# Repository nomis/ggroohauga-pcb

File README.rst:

Logitech® Z906 Surround Sound Speakers
======================================

Overview
--------

PCBs for an alternative console and simulated amplifier interface for the
ESP32-S3 microcontroller interacting with Logitech® Z906 Surround Sound
Speakers.

    Glod picked up his horn. Cliff sat down and found his hammers. Buddy walked
    to the centre of the stage and, to Cliff's amazement, just stood there
    looking down at his feet.

    The cheering began to subside. And then it died away altogether. The huge
    hall was filled with the hush of hundreds of people holding their breath.

    Buddy's fingers moved. He picked out three simple little chords. And then he
    looked up.

    "Hello, Ankh-Morpork!"

    Cliff felt the music rise up behind him and rush him forward into a tunnel
    of fire and sparks and excitement. He brought his hammers down. And it was
    Music With Rocks In.

    -- `Terry Pratchett <https://en.wikipedia.org/wiki/Terry_Pratchett>`_
    (`Soul Music, 1994 <https://en.wikipedia.org/wiki/Soul_Music_(novel)>`_)

Purpose
-------

Provide an unofficial alternative console (to control the amplifier directly
without the original console) and simulated amplifier interface (to indirectly
control an amplifier with the original console).

Usage
-----

This project is made up of 3 KiCad projects, each of which share the same common
schematic file. These projects depend on support for symbolic links (which
can be enabled in Developer Mode if you're using Windows).

Schematic
---------

Common schematic shared by all PCBs. Components with an "A-" (amplifier)
reference are for the amplifier/bridge PCBs, components with a "C-" (console)
reference are for the console/bridge PCBs and components with an "S-" (single
DE-15 socket) reference are for the amplifier/console PCBs.

.. image:: render/ggroohauga-shared-sch.svg
   :alt: Common schematic

Amplifier PCB
~~~~~~~~~~~~~

Connect to an amplifier on its own to control the amplifier and access the Aux
Input and Headphones audio through `3.5mm TRS sockets <https://en.wikipedia.org/wiki/Phone_connector_(audio)>`_.

Dimensions: 95mm W × 31mm H

.. image:: render/ggroohauga-amplifier-pcb.svg
   :alt: Front and back of amplifier PCB

.. image:: render/ggroohauga-amplifier-sch.svg
   :alt: Amplifier-specific schematic

Console PCB
~~~~~~~~~~~

Connect to a console on its own to control the console and access the Aux Input
and Headphones audio through `3.5mm TRS sockets <https://en.wikipedia.org/wiki/Phone_connector_(audio)>`_.

Dimensions: 95mm W × 31mm H

.. image:: render/ggroohauga-console-pcb.svg
   :alt: Front and back of console PCB

.. image:: render/ggroohauga-console-sch.svg
   :alt: Console-specific schematic

Bridge PCB
~~~~~~~~~~

Connect between an amplifier and a console to control both devices
independently.

Dimensions: 98.5mm W × 31mm H

.. image:: render/ggroohauga-bridge-pcb.svg
   :alt: Front and back of bridge PCB

.. image:: render/ggroohauga-bridge-sch.svg
   :alt: Bridge-specific schematic

Components
----------

+-------+--------------------------------------------------------+--------------------+
| Ref   | Name                                                   | PCB                |
+=======+========================================================+====================+
|       | ESP32-S3 Development Board                             | all                |
+-------+--------------------------------------------------------+--------------------+
| S3L1  | 1x20 Pin Socket, Through Hole (2.54mm)                 | all                |
+-------+--------------------------------------------------------+--------------------+
| S3R1  | 1x20 Pin Socket, Through Hole (2.54mm)                 | all                |
+-------+--------------------------------------------------------+--------------------+
| A-C1  | 0.1µF Capacitor, SMD 0805 (Metric 2012)                | amplifier, bridge  |
+-------+--------------------------------------------------------+--------------------+
| A-C2  | 0.1µF Capacitor, SMD 0805 (Metric 2012)                | amplifier, bridge  |
+-------+--------------------------------------------------------+--------------------+
| A-J1  | Amphenol L77HDE15SD1CH4R DE-15 socket                  | amplifier, bridge  |
+-------+--------------------------------------------------------+--------------------+
| A-R1  | 1kΩ Resistor, SMD 0805 (Metric 2012)                   | amplifier, bridge  |
+-------+--------------------------------------------------------+--------------------+
| A-R2  | 10kΩ Resistor, SMD 0805 (Metric 2012)                  | amplifier, bridge  |
+-------+--------------------------------------------------------+--------------------+
| A-R3  | 10kΩ Resistor, SMD 0805 (Metric 2012)                  | amplifier, bridge  |
+-------+--------------------------------------------------------+--------------------+
| A-U1  | Texas Instruments ISO6742DWR Digital Isolator, SOIC-16 | amplifier, bridge  |
+-------+--------------------------------------------------------+--------------------+
| C-J1  | Amphenol L717HDE15PD1CH4F DE-15 plug                   | console, bridge    |
+-------+--------------------------------------------------------+--------------------+
| C-Q1  | Diodes DMP2004K P-Channel MOSFET, SOT-23-3             | console, bridge    |
+-------+--------------------------------------------------------+--------------------+
| S-J1  | Same Sky SJ1-3523N 3.5mm Audio Jack                    | amplifier, console |
+-------+--------------------------------------------------------+--------------------+
| S-J2  | Same Sky SJ1-3523N 3.5mm Audio Jack                    | amplifier, console |
+-------+--------------------------------------------------------+--------------------+

Supported ESP32-S3 Boards
-------------------------

* WEMOS LOLIN S3
* Espressif ESP32-S3-DevKitC-1
* Espressif ESP32-S3-DevKitM-1

Amplifier Signals GPIOs
~~~~~~~~~~~~~~~~~~~~~~~

"Amplifier Power In" should only be pulled down, to avoid back-powering the
amplifier microcontroller when mains power is off.

When "Amplifier Power In" is active, the amplifier has mains power. Enable
"Console Announce" to turn the amplifier on, and disable it turn the amplifier
off. Don't leave it on constantly because it will heat up and waste power.
Automatic standby can be implemented by
`reading the idle time <https://github.com/nomis/logitech-z906/blob/main/protocol.rst#read-idle-time>`_.

When "Amplifier Detect" is active, the amplifier is ready to communicate over
the 3.3V UART. The labels "Amplifier RX" and "Amplifier TX" are from the
perspective of the amplifier.

+------------------------+-------+---------+-----------+-----------+----------+----------+
| Name                   |  Pin  |  LOLIN  |  DevKitC  |  DevKitM  |  Socket  |  Active  |
+========================+=======+=========+===========+===========+==========+==========+
| Amplifier Power In     |   11  |    8    |     8     |    10     |   L 12   |   High   |
+------------------------+-------+---------+-----------+-----------+----------+----------+
| Console Announce       |   15  |   41    |    41     |    42     |   R  7   |   Low    |
+------------------------+-------+---------+-----------+-----------+----------+----------+
| Amplifier Detect       |    8  |   21    |    21     |    21     |   R 15   |   Low    |
+------------------------+-------+---------+-----------+-----------+----------+----------+
| Amplifier RX           |   13  |   10    |    10     |    14     |   L 16   |          |
+------------------------+-------+---------+-----------+-----------+----------+----------+
| Amplifier TX           |   12  |    9    |     9     |    13     |   L 15   |          |
+------------------------+-------+---------+-----------+-----------+----------+----------+
| 3.3V                   |       |         |           |           |   L  1   |          |
+------------------------+-------+---------+-----------+-----------+----------+----------+
| GND                    |    6  |         |           |           |   R  1   |          |
+------------------------+-------+---------+-----------+-----------+----------+----------+

Console Signals GPIOs
~~~~~~~~~~~~~~~~~~~~~

Prepare all other GPIOs and UARTs before applying console power, otherwise it
will report a communication error.

Enable "Console Power out" to power the console on, and disable it to power off
the console. Without a `firmware modification to the console <https://github.com/nomis/logitech-z906/blob/main/firmware.rst#automatic-power-on>`_,
user intervention will be required to turn the console on after it's powered.

When "Amplifier Announce" is active, the amplifier indicates that it is ready to
communicate over the 3.3V UART. The labels "Console RX" and "Console TX" are
from the perspective of the console.

+------------------------+-------+---------+-----------+-----------+----------+----------+
| Name                   |  Pin  |  LOLIN  |  DevKitC  |  DevKitM  |  Socket  |  Active  |
+========================+=======+=========+===========+===========+==========+==========+
| Console Power Out      |   11  |   40    |    40     |    41     |   R  8   |   Low    |
+------------------------+-------+---------+-----------+-----------+----------+----------+
| Console RX             |   12  |    4    |     4     |     2     |   L  4   |          |
+------------------------+-------+---------+-----------+-----------+----------+----------+
| Console TX             |   13  |    6    |     6     |     4     |   L  6   |          |
+------------------------+-------+---------+-----------+-----------+----------+----------+
| Amplifier Announce     |    8  |   13    |    47     |    26     |   R 17   |   Low    |
+------------------------+-------+---------+-----------+-----------+----------+----------+
| Console Detect         |   15  |   17    |    17     |     8     |   L 10   |   Low    |
+------------------------+-------+---------+-----------+-----------+----------+----------+
| 3.3V                   |       |         |           |           |   L  1   |          |
+------------------------+-------+---------+-----------+-----------+----------+----------+
| GND                    |    6  |         |           |           |   R  1   |          |
+------------------------+-------+---------+-----------+-----------+----------+----------+

Board ID GPIOs
~~~~~~~~~~~~~~

To identify which type of PCB the ESP32-S3 has been connected to, read the
big-endian value of these GPIOs.

+-------+---------+-----------+-----------+
|  Bit  |  LOLIN  |  DevKitC  |  DevKitM  |
+=======+=========+===========+===========+
|   2   |    7    |     7     |     5     |
+-------+---------+-----------+-----------+
|   1   |   15    |    15     |     6     |
+-------+---------+-----------+-----------+
|   0   |   16    |    16     |     7     |
+-------+---------+-----------+-----------+

+---------+-----------+
| Value   | PCB       |
+=========+===========+
| 000 (0) | Amplifier |
+---------+-----------+
| 001 (1) | Bridge    |
+---------+-----------+
| 010 (2) | Console   |
+---------+-----------+

Related Documentation
---------------------

* `Console firmware/interface/protocol <https://github.com/nomis/logitech-z906>`_

Related Software
----------------

* `Software to interact with the console/amplifier <https://github.com/nomis/ggroohauga>`_

Notices
-------

"Logitech" is a trademark of `Logitech International SA <https://www.logitech.com/>`_.

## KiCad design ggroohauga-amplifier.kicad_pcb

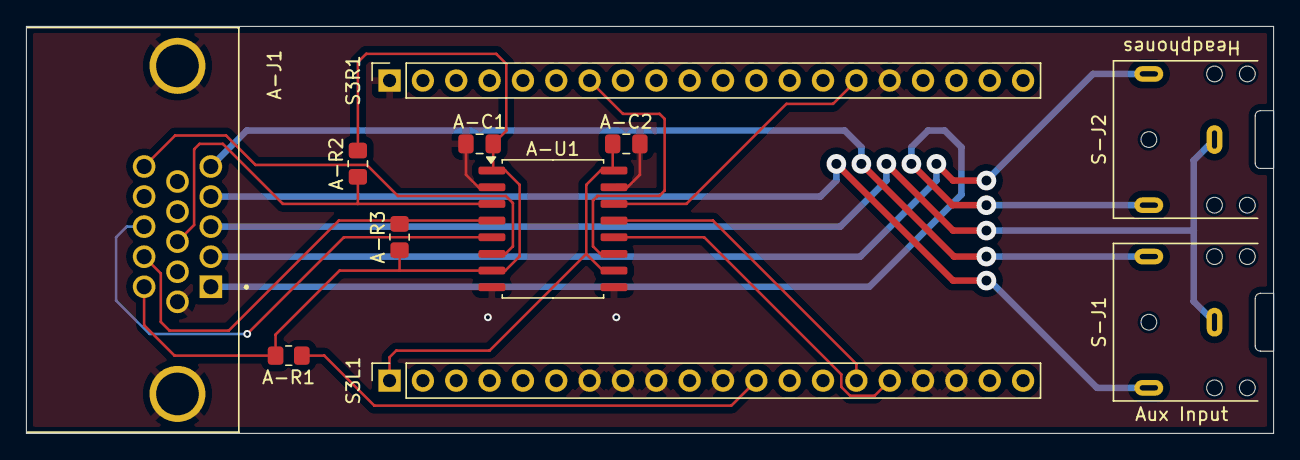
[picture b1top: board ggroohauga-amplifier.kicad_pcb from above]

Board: 2 copper layers, 95.0 x 31.0 mm, 12 parts (1 on the bottom side), 17 nets.

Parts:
A-C1, A-C2: 0.1µF; C_0805_2012Metric_Pad1.18x1.45mm_HandSolder
A-J1: DE15_Socket_HighDensity_MountingHoles; AMPHENOL_L77HDE15SD1CH4R
A-R1: 1kΩ; R_0805_2012Metric_Pad1.20x1.40mm_HandSolder
A-R2, A-R3: 10kΩ; R_0805_2012Metric_Pad1.20x1.40mm_HandSolder
A-U1: ISO6742; SOIC-16W_7.5x10.3mm_P1.27mm
MUSICWITHROCKSIN: LOGO
S3L1, S3R1: Conn_01x20_Socket; PinSocket_1x20_P2.54mm_Vertical
S-J1: Aux Input; Jack_3.5mm_CUI_SJ1-3523N_Horizontal
S-J2: Headphones; Jack_3.5mm_CUI_SJ1-3523N_Horizontal

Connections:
+3.3V: A-C2.1, A-U1.10 (EN2), A-U1.16 (V_{CC2}), S3L1.1
/Common/AMP_POWER_IN: A-C1.1, A-J1.11, A-R1.2, A-R2.2, A-R3.1, A-U1.1 (V_{CC1}), A-U1.7 (EN1)
/Common/AMP_RX: A-J1.13, A-U1.5 (OUTC)
/Common/AMP_TX: A-J1.12, A-R3.2, A-U1.4 (INB)
/Common/GPIO_L8_C8_M10/AMP_POWER_IN: A-R1.1, S3L1.12
/Common/GPIO_L9_C9_M13/AMP_TX: A-U1.13 (OUTB), S3L1.15
/Common/GPIO_L10_C10_M14/AMP_RX: A-U1.12 (INC), S3L1.16
/Common/~AMP_DETECT: A-J1.8, A-R2.1, A-U1.3 (INA)
/Common/~CON_ANNOUNCE: A-J1.15, A-U1.6 (OUTD)
/Common/~GPIO_L21_C21_M21/AMP_DETECT: A-U1.14 (OUTA), S3R1.15
/Common/~GPIO_L41_C41_M42/CON_ANNOUNCE: A-U1.11 (IND), S3R1.7
AUDIO_AUX_L: A-J1.5, S-J1.T
AUDIO_AUX_R: A-J1.4, S-J1.R
AUDIO_GROUND: A-J1.3, S-J1.S, S-J2.S
AUDIO_HEADPHONES_L: A-J1.2, S-J2.T
AUDIO_HEADPHONES_R: A-J1.1, S-J2.R
GND: A-C1.2, A-C2.2, A-J1.0, A-J1.6, A-U1.2 (GND1), A-U1.8 (GND1), A-U1.9 (GND2), A-U1.15 (GND2), S3L1.7, S3L1.8, S3L1.9, S3L1.11, S3L1.17, S3L1.18, S3R1.1, S3R1.16

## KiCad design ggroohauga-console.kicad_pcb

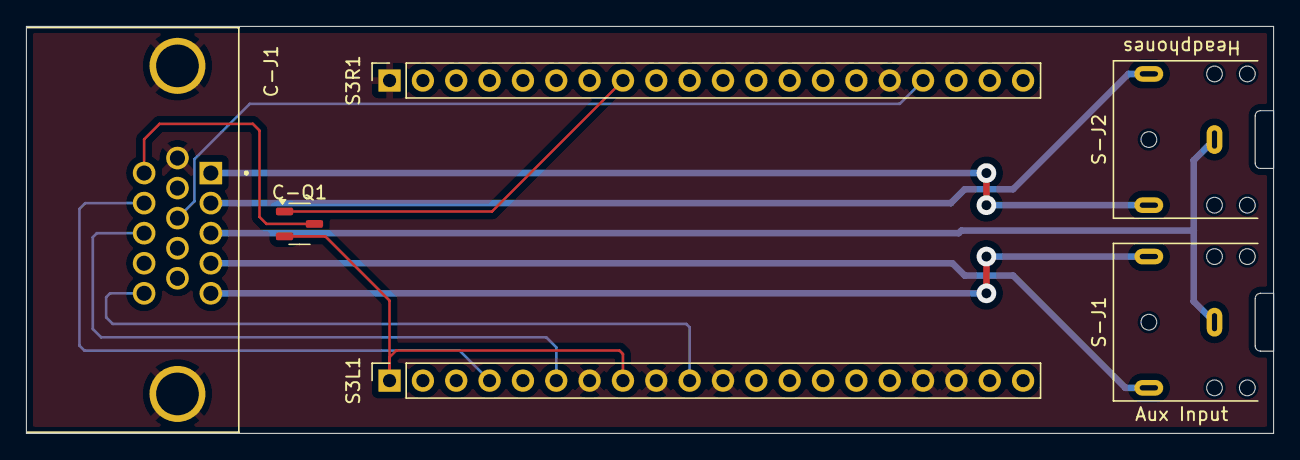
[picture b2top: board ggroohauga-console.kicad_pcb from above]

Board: 2 copper layers, 95.0 x 31.0 mm, 7 parts (1 on the bottom side), 13 nets.

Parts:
C-J1: DE15_Pins_HighDensity_MountingHoles; AMPHENOL_L717HDE15PD1CH4F
C-Q1: DMP2004K; SOT-23-3
MUSICWITHROCKSIN: LOGO
S3L1, S3R1: Conn_01x20_Socket; PinSocket_1x20_P2.54mm_Vertical
S-J1: Aux Input; Jack_3.5mm_CUI_SJ1-3523N_Horizontal
S-J2: Headphones; Jack_3.5mm_CUI_SJ1-3523N_Horizontal

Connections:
+3.3V: C-Q1.2 (S), S3L1.1, S3L1.8
/Common/CON_POWER_OUT: C-J1.11, C-Q1.3 (D)
/Common/GPIO_L4_C4_M2/CON_RX: C-J1.12, S3L1.4
/Common/GPIO_L6_C6_M4/CON_TX: C-J1.13, S3L1.6
/Common/~GPIO_L13_C47_M26/AMP_ANNOUNCE: C-J1.8, S3R1.17
/Common/~GPIO_L17_C17_M8/CON_DETECT: C-J1.15, S3L1.10
/Common/~GPIO_L40_C40_M41/CON_POWER_OUT: C-Q1.1 (G), S3R1.8
AUDIO_AUX_L: C-J1.5, S-J1.T
AUDIO_AUX_R: C-J1.4, S-J1.R
AUDIO_GROUND: C-J1.3, S-J1.S, S-J2.S
AUDIO_HEADPHONES_L: C-J1.2, S-J2.T
AUDIO_HEADPHONES_R: C-J1.1, S-J2.R
GND: C-J1.0, C-J1.6, S3L1.7, S3L1.9, S3L1.11, S3L1.17, S3L1.18, S3R1.1, S3R1.16

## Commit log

2025-03-25 Create amplifier PCB
2025-03-26 Add README file and reorganise shared files
2025-03-26 List ESP32-S3 boards that the PCBs will support
2025-03-26 Create console PCB
2025-03-26 Create bridge PCB
2025-03-27 Mirror silkscreen text on the bottom
2025-03-28 Align PCBs to whole mils
2025-03-28 Create Gerber files
2025-03-28 Add Gerber files for JLCPCB
2025-03-30 Fix compatibility with ESP32-S3-DevKitM-1
2025-04-08 Unhide the S3L1 silkscreen reference
2025-04-16 Connect audio pins on the bridge PCB
2025-04-17 Use thicker traces and vias for audio connections
2025-04-21 Fix silkscreen overlap
2025-04-21 Move stuff around
2025-04-21 Mark audio inputs/outputs differently
2025-04-21 Rotate MOSFET pins so that it's connected correctly
2025-04-22 Move resistor on the amplifier too
2025-04-23 Fix DE-15 connector footprint so that the shield is automatically GND
2025-04-23 Fix console oid
2025-04-23 Update Gerber files for JLCPCB
2025-04-26 Document the GPIOs for each board
2025-04-26 Document pin socket numbers
2025-04-26 Document socket positions of 3.3V and GND
2025-04-26 Add active high/low information
2025-06-05 Cleanup tracks
2025-06-05 Ignore zip files
2025-06-08 Render the PCB as an image
2025-06-08 Remove title from SVGs
2025-06-10 Add components list
2025-06-25 Fix PCB images
2025-06-25 Convert to KiCad 9.0 format
2025-06-25 Add 4ch digital isolator and 2 TRS jacks to the schematic
2025-06-25 Add 4ch digital isolator and 2 TRS jacks to the amplifier PCB
2025-06-25 Label other GPIOs
2025-06-25 Reorganise schematic into multiple sheets and add 3 board identifier GPIOs
2025-06-25 Add 4ch digital isolator to the bridge PCB
2025-06-25 Ground unused GPIOs
2025-06-25 Move bridge text out of the way of vias and cleanup tracks
2025-06-25 Make amplifier PCB longer to accommodate the extra 2 pins on DevKit boards
2025-06-26 Add "BOARD_ID" to the GPIOs for that and fix net names on unused GPIOs
2025-06-27 The igital isolator should prevent back-powering on data pins
2025-06-27 Make all the PCBs a regular size, to 0.5mm
2025-06-27 Add 2 TRS jacks to the console PCB
2025-06-27 Show "Headphones" and "Aux In" labels on PCBs
2025-06-27 Show extra 2 pins clearance measurements on all PCBs
2025-06-27 Remove unnecessary symlink
2025-06-27 Add pull-up resistors to amplifier detect and RX inputs
2025-06-27 Use consistent position of audio vias and rear silkscreen
2025-06-28 Move some stuff around on the schematic
2025-06-28 Render schematics
2025-06-28 Fix component references for audio jacks
2025-06-28 Document board ID GPIOs
2025-06-29 Add "music with rocks in" image
2025-06-29 Update schematic render
2025-06-29 Make bottom PCB the right way up and use the same size for all PCB images
2025-06-29 Realign amplifier and bridge PCBs so that they match
2025-06-29 Fix thin lines in image
2025-06-29 Rename "Aux In" to "Aux Input" and document 3.5mm audio sockets
2025-07-04 Move pull-up from AMP_RX to AMP_TX
2025-07-05 Fix GPIO assignments
    Stop using GPIO 14 because the pull-up isn't working reliably on my LOLIN
    S3 board even when floating and I don't have another one to test it with.
    Don't use GPIO 35 on the DevKitC-1 board because that conflicts with the
    Octal PSRAM.
2025-07-05 Name the two different 3.3V power flags
2025-07-06 Refill
2025-07-06 Add make file for zip files
2025-07-06 Fix edge cuts on audio connectors
2025-07-13 Fix headphones label direction
2025-07-13 Add 3D models of the DE-15 connectors and realign some tracks
2025-07-20 Add Discworld quote
2025-07-20 Add more explanation of how to use the GPIOs
2025-07-20 Indicate active low signals on the schematic
2025-07-20 Add PCB dimensions
2025-07-21 Use the better SOT-23-3 footprint for C-Q1
2025-07-27 Use shorter PCB URLs
